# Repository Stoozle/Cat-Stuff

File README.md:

# FLOPS (FeLine Obesity Prevention System)
## High level description (project in development and much is subject to change and refinement)
* Cat owner's may want to monitor their cat's weight for various reasons. This project is intended to provide a system that will automatically measures a cat's weight. Measurement data can be used to inform appropriate modifications to a cat's diet in order to meet a target weight.
## Theory of operation
* Takes a cat's weight measurement every time it sleeps in its bed
* Allows user to observe plot of weight measurements over time

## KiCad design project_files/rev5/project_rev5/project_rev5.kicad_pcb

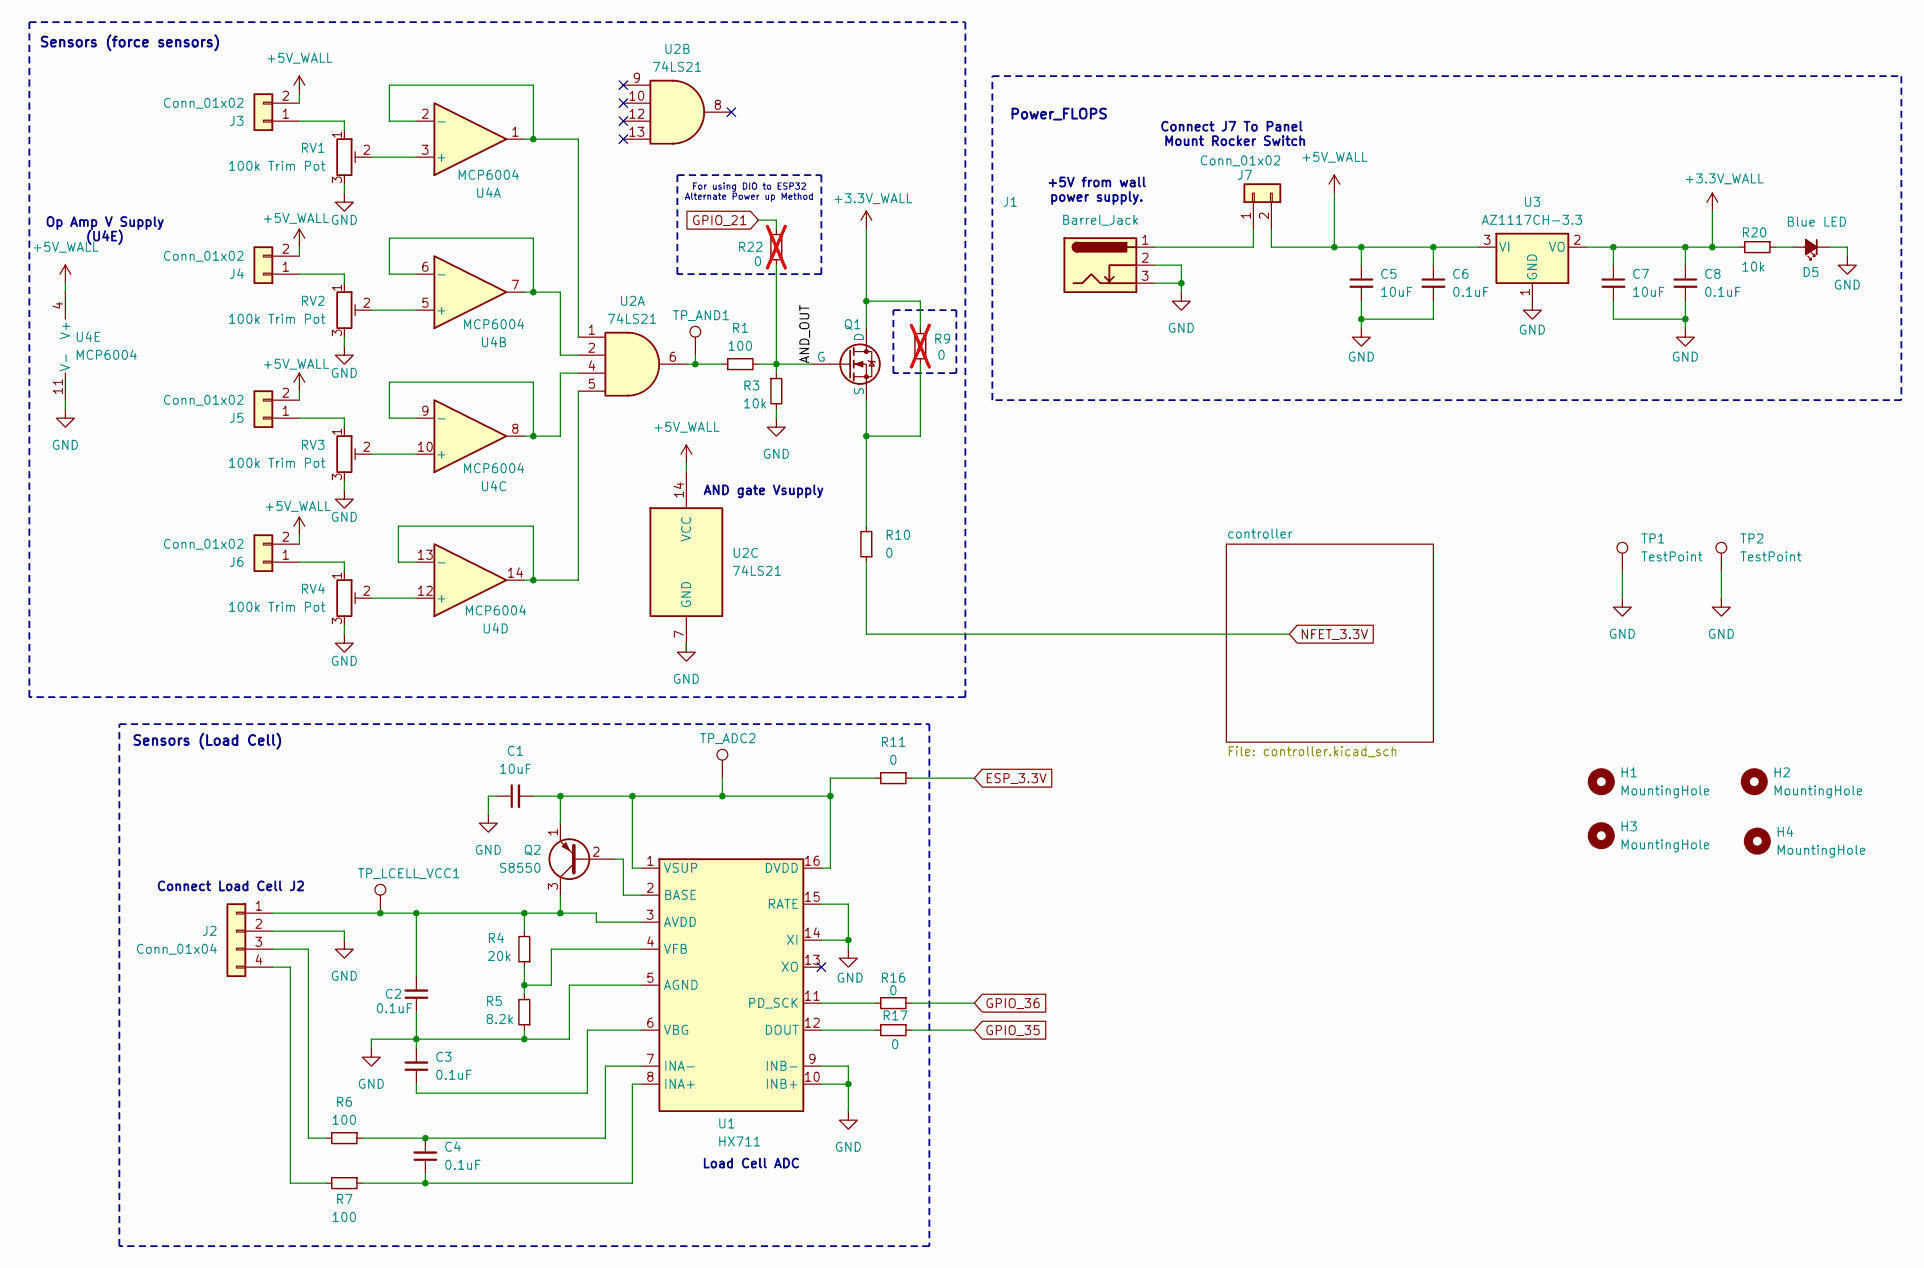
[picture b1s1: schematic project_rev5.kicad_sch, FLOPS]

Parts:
C1, C5, C7: 10uF; C_0603_1608Metric_Pad1.08x0.95mm_HandSolder
C2, C3, C4, C6, C8: 0.1uF; C_0603_1608Metric_Pad1.08x0.95mm_HandSolder
D5: 150060BS75000; LED_0603_1608Metric
H1, H2, H3, H4: MountingHole; MountingHole_3.2mm_M3_Pad
J1: Barrel_Jack; BarrelJack_Kycon_KLDX-0202-xC_Horizontal
J2: Conn_01x04; JST_XA_S04B-XASK-1N-BN_1x04_P2.50mm_Horizontal
J3, J4, J5, J6, J7: Conn_01x02; JST_XA_S02B-XASK-1N-BN_1x02_P2.50mm_Horizontal
Q1: BSS816NWH6327XTSA1; SOT-323_SC-70
Q2: S8550; SOT-23-3
R1, R6, R7: 100; R_0603_1608Metric_Pad0.98x0.95mm_HandSolder
R3, R20: 10k; R_0603_1608Metric_Pad0.98x0.95mm_HandSolder
R4: 20k; R_0603_1608Metric_Pad0.98x0.95mm_HandSolder
R5: 8.2k; R_0603_1608Metric_Pad0.98x0.95mm_HandSolder
R9, R22: 0; R_0603_1608Metric_Pad0.98x0.95mm_HandSolder; not fitted
R10, R11, R16, R17: 0; R_0603_1608Metric_Pad0.98x0.95mm_HandSolder
RV1, RV2, RV3, RV4: 100k Trim Pot; Potentiometer_Bourns_TC33X_Vertical
TP1, TP2: TestPoint; TestPoint_Keystone_5015_Micro-Minature
TP_ADC2: TestPoint; TestPoint_THTPad_D1.5mm_Drill0.7mm
TP_AND1: TestPoint; TestPoint_THTPad_D1.5mm_Drill0.7mm
TP_LCELL_VCC1: TestPoint; TestPoint_THTPad_D1.5mm_Drill0.7mm
U1: HX711; SOP-16_3.9x9.9mm_P1.27mm
U2: 74LS21; SOIC-14_3.9x8.7mm_P1.27mm
U3: AZ1117CH-3.3; SOT-223-3_TabPin2
U4: MCP6004; SOIC-14_3.9x8.7mm_P1.27mm

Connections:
+3.3V_WALL: C7.1, C8.1, Q1.1 (D), R9.2, R20.2, U3.2 (VO)
+5V_WALL: C5.1, C6.1, J3.2, J4.2, J5.2, J6.2, J7.2, U2.14 (VCC), U3.3 (VI), U4.4 (V+)
/AND_OUT: Q1.2 (G), R1.2, R3.1, R22.1
ESP_3.3V: R11.1; also elsewhere on the board
GND: C1.1, C2.1, C3.2, C5.2, C6.2, C7.2, C8.2, D5.1 (K), J1.2, J1.3, J2.2, R3.2, R5.1, RV1.3, RV2.3, RV3.3, RV4.3, TP1.1, TP2.1, U1.5 (AGND), U1.9 (INB-), U1.10 (INB+), U1.14 (XI), U1.15 (RATE), U2.7 (GND), U3.1 (GND), U4.11 (V-); also elsewhere on the board
GPIO_21: R22.2; also elsewhere on the board
GPIO_35: R17.1; also elsewhere on the board
GPIO_36: R16.1; also elsewhere on the board
NFET_3.3V: R10.1; also elsewhere on the board
unnamed: D5.2 (A), R20.1
unnamed: C2.2, J2.1, Q2.3 (C), R4.2, TP_LCELL_VCC1.1, U1.3 (AVDD)
unnamed: J2.3, R6.2
unnamed: J2.4, R7.2
unnamed: J3.1, RV1.1
unnamed: J4.1, RV2.1
unnamed: J5.1, RV3.1
unnamed: J6.1, RV4.1
unnamed: J1.1, J7.1
unnamed: Q1.3 (S), R9.1, R10.2
unnamed: Q2.2 (B), U1.2 (BASE)
unnamed: C1.2, Q2.1 (E), R11.2, TP_ADC2.1, U1.1 (VSUP), U1.16 (DVDD)
unnamed: R1.1, TP_AND1.1, U2.6
unnamed: R17.2, U1.12 (DOUT)
unnamed: C4.1, R7.1, U1.8 (INA+)
unnamed: C4.2, R6.1, U1.7 (INA-)
unnamed: R16.2, U1.11 (PD_SCK)
unnamed: C3.1, U1.6 (VBG)
unnamed: R4.1, R5.2, U1.4 (VFB)
unnamed: RV1.2, U4.3 (+)
unnamed: U2.1, U4.1, U4.2 (-)
unnamed: RV2.2, U4.5 (+)
unnamed: U2.2, U4.6 (-), U4.7
unnamed: RV3.2, U4.10 (+)
unnamed: U2.4, U4.8, U4.9 (-)
unnamed: RV4.2, U4.12 (+)
unnamed: U2.5, U4.13 (-), U4.14

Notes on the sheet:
Connect J7 To Panel Mount Rocker Switch
Power_FLOPS
+5V from wall power supply.
Op Amp V Supply (U4E)
Sensors (Load Cell)
Load Cell ADC
For using DIO to ESP32 Alternate Power up Method
Sensors (force sensors)
Connect Load Cell J2
AND gate Vsupply

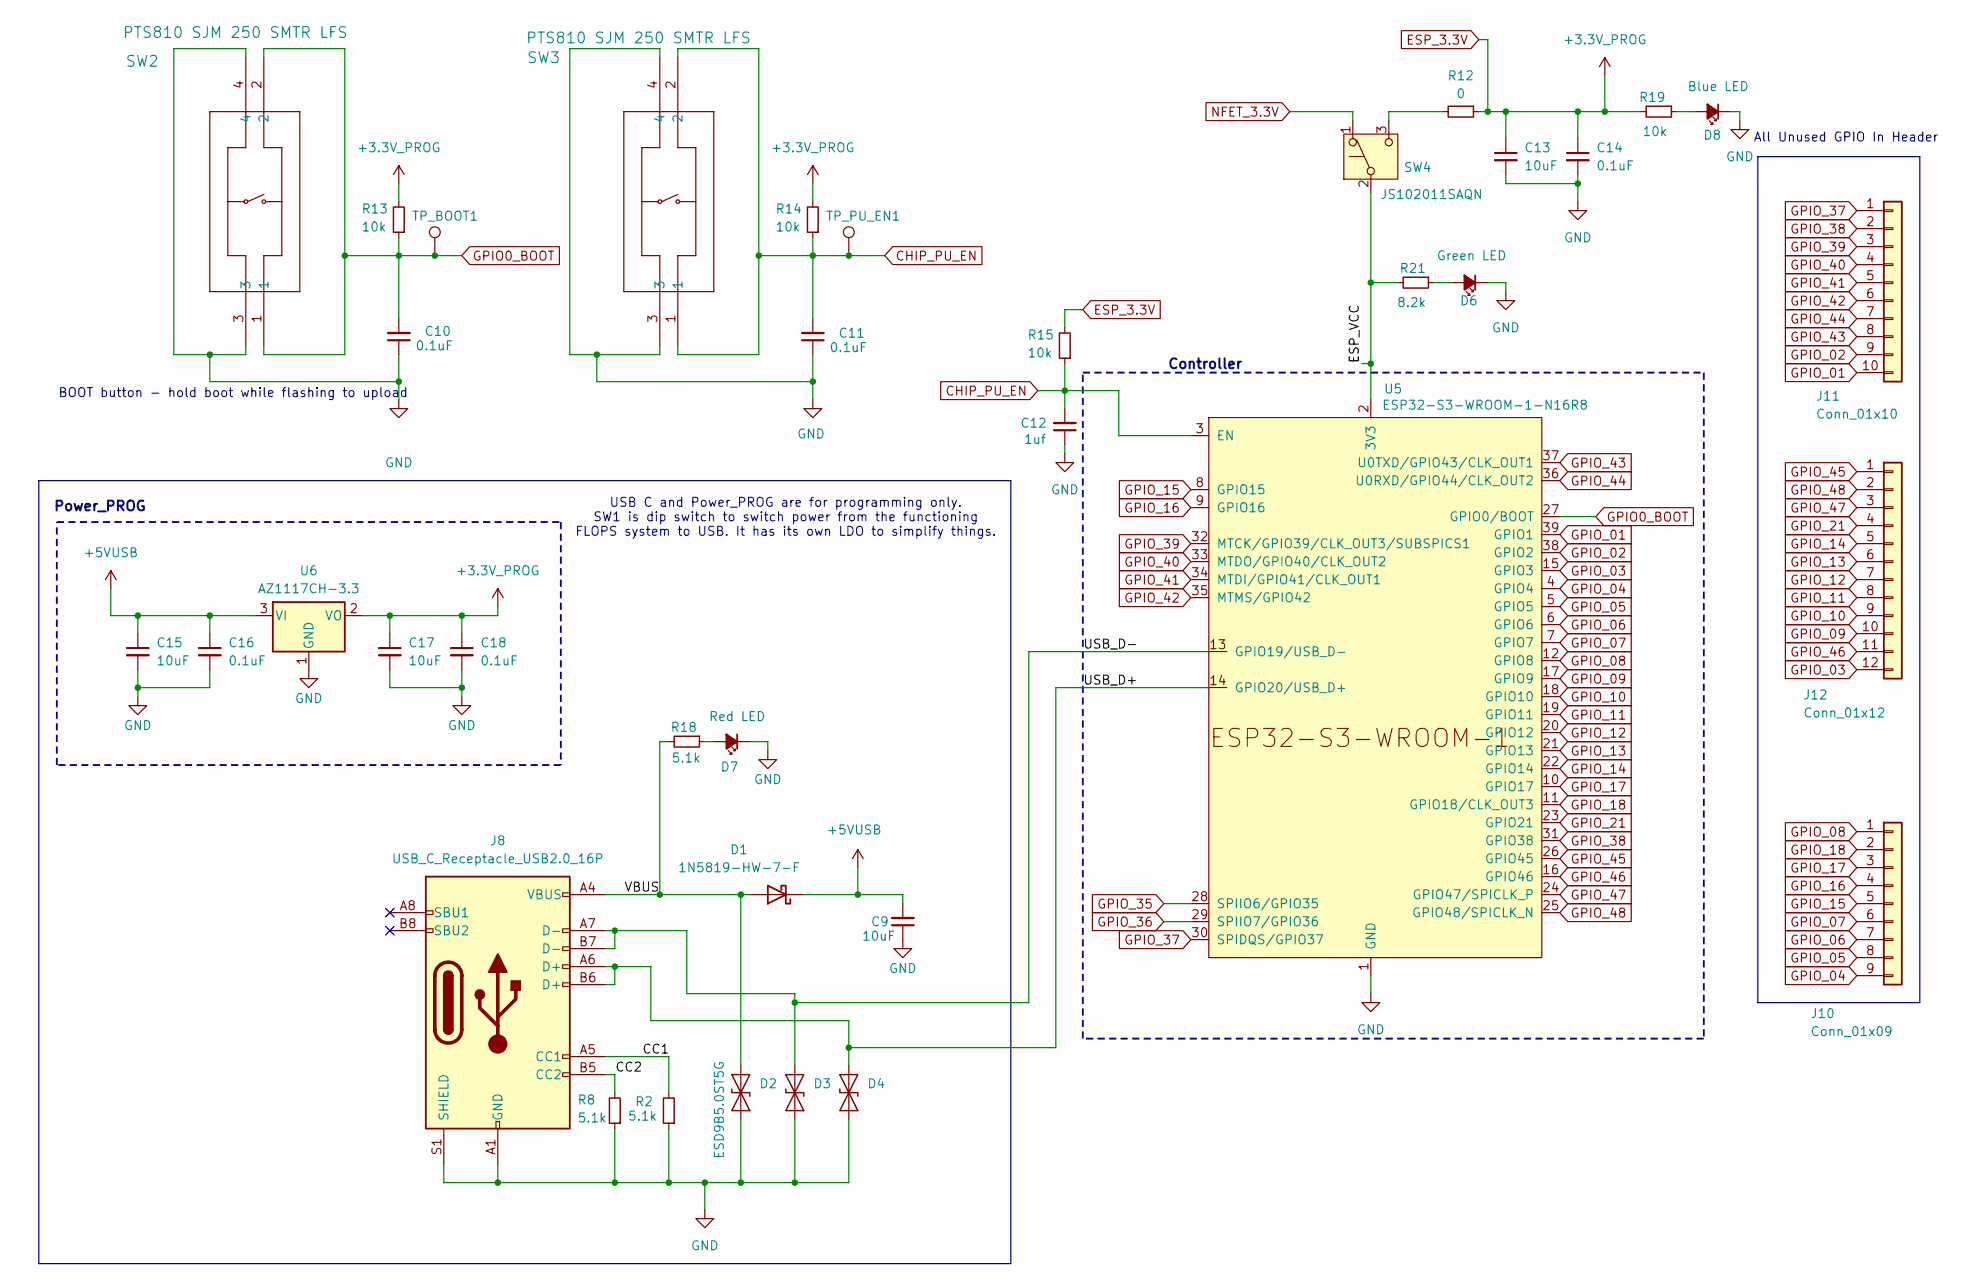
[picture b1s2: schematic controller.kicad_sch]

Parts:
C9, C13, C15, C17: 10uF; C_0603_1608Metric_Pad1.08x0.95mm_HandSolder
C10, C11, C14, C16, C18: 0.1uF; C_0603_1608Metric_Pad1.08x0.95mm_HandSolder
C12: 1uf; C_0603_1608Metric_Pad1.08x0.95mm_HandSolder
D1: 1N5819-HW-7-F; D_SOD-123
D2, D3, D4: ESD9B5.0ST5G; D_SOD-923
D6, D8: 150060BS75000; LED_0603_1608Metric
D7: 150060RS75000; LED_0603_1608Metric
J8: USB_C_Receptacle_USB2.0_16P; USB_C_Receptacle_GCT_USB4105-xx-A_16P_TopMnt_Horizontal
J10: Conn_01x09; PinHeader_1x09_P2.54mm_Vertical
J11: Conn_01x10; PinHeader_1x10_P2.54mm_Vertical
J12: Conn_01x12; PinHeader_1x12_P2.54mm_Vertical
R2, R8, R18: 5.1k; R_0603_1608Metric_Pad0.98x0.95mm_HandSolder
R12: 0; R_0603_1608Metric_Pad0.98x0.95mm_HandSolder
R13, R14, R15, R19: 10k; R_0603_1608Metric_Pad0.98x0.95mm_HandSolder
R21: 8.2k; R_0603_1608Metric_Pad0.98x0.95mm_HandSolder
SW2, SW3: PTS810 SJM 250 SMTR LFS; PTS810_CNK
SW4: JS102011SAQN; SW_SPDT_CK_JS102011SAQN
TP_BOOT1: TestPoint; TestPoint_THTPad_D1.5mm_Drill0.7mm
TP_PU_EN1: TestPoint; TestPoint_THTPad_D1.5mm_Drill0.7mm
U5: ESP32-S3-WROOM-1-N16R8; ESP32-S3-WROOM-1
U6: AZ1117CH-3.3; SOT-223-3_TabPin2

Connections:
+5VUSB: C9.2, C15.1, C16.1, D1.1 (K), U6.3 (VI)
/controller/CC1: J8.A5 (CC1), R2.2
/controller/CC2: J8.B5 (CC2), R8.2
/controller/ESP_VCC: R21.2, SW4.2 (B), U5.2 (3V3)
/controller/USB_D+: D4.1 (A1), J8.A6 (D+), J8.B6 (D+), U5.14 (GPIO20/USB_D+)
/controller/USB_D-: D3.1 (A1), J8.A7 (D-), J8.B7 (D-), U5.13 (GPIO19/USB_D-)
/controller/VBUS: D1.2 (A), D2.1 (A1), J8.A4 (VBUS), J8.A9 (VBUS), J8.B4 (VBUS), J8.B9 (VBUS), R18.2
CHIP_PU_EN: C11.2, C12.2, R14.1, R15.1, SW3.1, SW3.2, TP_PU_EN1.1, U5.3 (EN)
ESP_3.3V: C13.1, C14.1, C17.1, C18.1, R12.1, R13.2, R14.2, R15.2, R19.2, U6.2 (VO); also elsewhere on the board
GND: C9.1, C10.1, C11.1, C12.1, C13.2, C14.2, C15.2, C16.2, C17.2, C18.2, D2.2 (A2), D3.2 (A2), D4.2 (A2), D6.1 (K), D7.1 (K), D8.1 (K), J8.A1 (GND), J8.A12 (GND), J8.B1 (GND), J8.B12 (GND), J8.S1 (SHIELD), R2.1, R8.1, SW2.3, SW2.4, SW3.3, SW3.4, U5.1 (GND), U5.40 (GND), U5.41 (GND), U6.1 (GND); also elsewhere on the board
GPIO0_BOOT: C10.2, R13.1, SW2.1, SW2.2, TP_BOOT1.1, U5.27 (GPIO0/BOOT)
GPIO_01: J11.10, U5.39 (GPIO1)
GPIO_02: J11.9, U5.38 (GPIO2)
GPIO_03: J12.12, U5.15 (GPIO3)
GPIO_04: J10.9, U5.4 (GPIO4)
GPIO_05: J10.8, U5.5 (GPIO5)
GPIO_06: J10.7, U5.6 (GPIO6)
GPIO_07: J10.6, U5.7 (GPIO7)
GPIO_08: J10.1, U5.12 (GPIO8)
GPIO_09: J12.10, U5.17 (GPIO9)
GPIO_10: J12.9, U5.18 (GPIO10)
GPIO_11: J12.8, U5.19 (GPIO11)
GPIO_12: J12.7, U5.20 (GPIO12)
GPIO_13: J12.6, U5.21 (GPIO13)
GPIO_14: J12.5, U5.22 (GPIO14)
GPIO_15: J10.5, U5.8 (GPIO15)
GPIO_16: J10.4, U5.9 (GPIO16)
GPIO_17: J10.3, U5.10 (GPIO17)
GPIO_18: J10.2, U5.11 (GPIO18/CLK_OUT3)
GPIO_21: J12.4, U5.23 (GPIO21); also elsewhere on the board
GPIO_35: U5.28 (SPIIO6/GPIO35); also elsewhere on the board
GPIO_36: U5.29 (SPIIO7/GPIO36); also elsewhere on the board
GPIO_37: J11.1, U5.30 (SPIDQS/GPIO37)
GPIO_38: J11.2, U5.31 (GPIO38)
GPIO_39: J11.3, U5.32 (MTCK/GPIO39/CLK_OUT3/SUBSPICS1)
GPIO_40: J11.4, U5.33 (MTDO/GPIO40/CLK_OUT2)
GPIO_41: J11.5, U5.34 (MTDI/GPIO41/CLK_OUT1)
GPIO_42: J11.6, U5.35 (MTMS/GPIO42)
GPIO_43: J11.8, U5.37 (U0TXD/GPIO43/CLK_OUT1)
GPIO_44: J11.7, U5.36 (U0RXD/GPIO44/CLK_OUT2)
GPIO_45: J12.1, U5.26 (GPIO45)
GPIO_46: J12.11, U5.16 (GPIO46)
GPIO_47: J12.3, U5.24 (GPIO47/SPICLK_P)
GPIO_48: J12.2, U5.25 (GPIO48/SPICLK_N)
NFET_3.3V: SW4.1 (A); also elsewhere on the board
unnamed: D6.2 (A), R21.1
unnamed: D7.2 (A), R18.1
unnamed: D8.2 (A), R19.1
unnamed: R12.2, SW4.3 (C)

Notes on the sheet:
Controller
All Unused GPIO In Header
USB C and Power_PROG are for programming only. SW1 is dip switch to switch power from the functioning FLOPS system to USB. It has its own LDO to simplify things.
BOOT button - hold boot while flashing to upload
Power_PROG

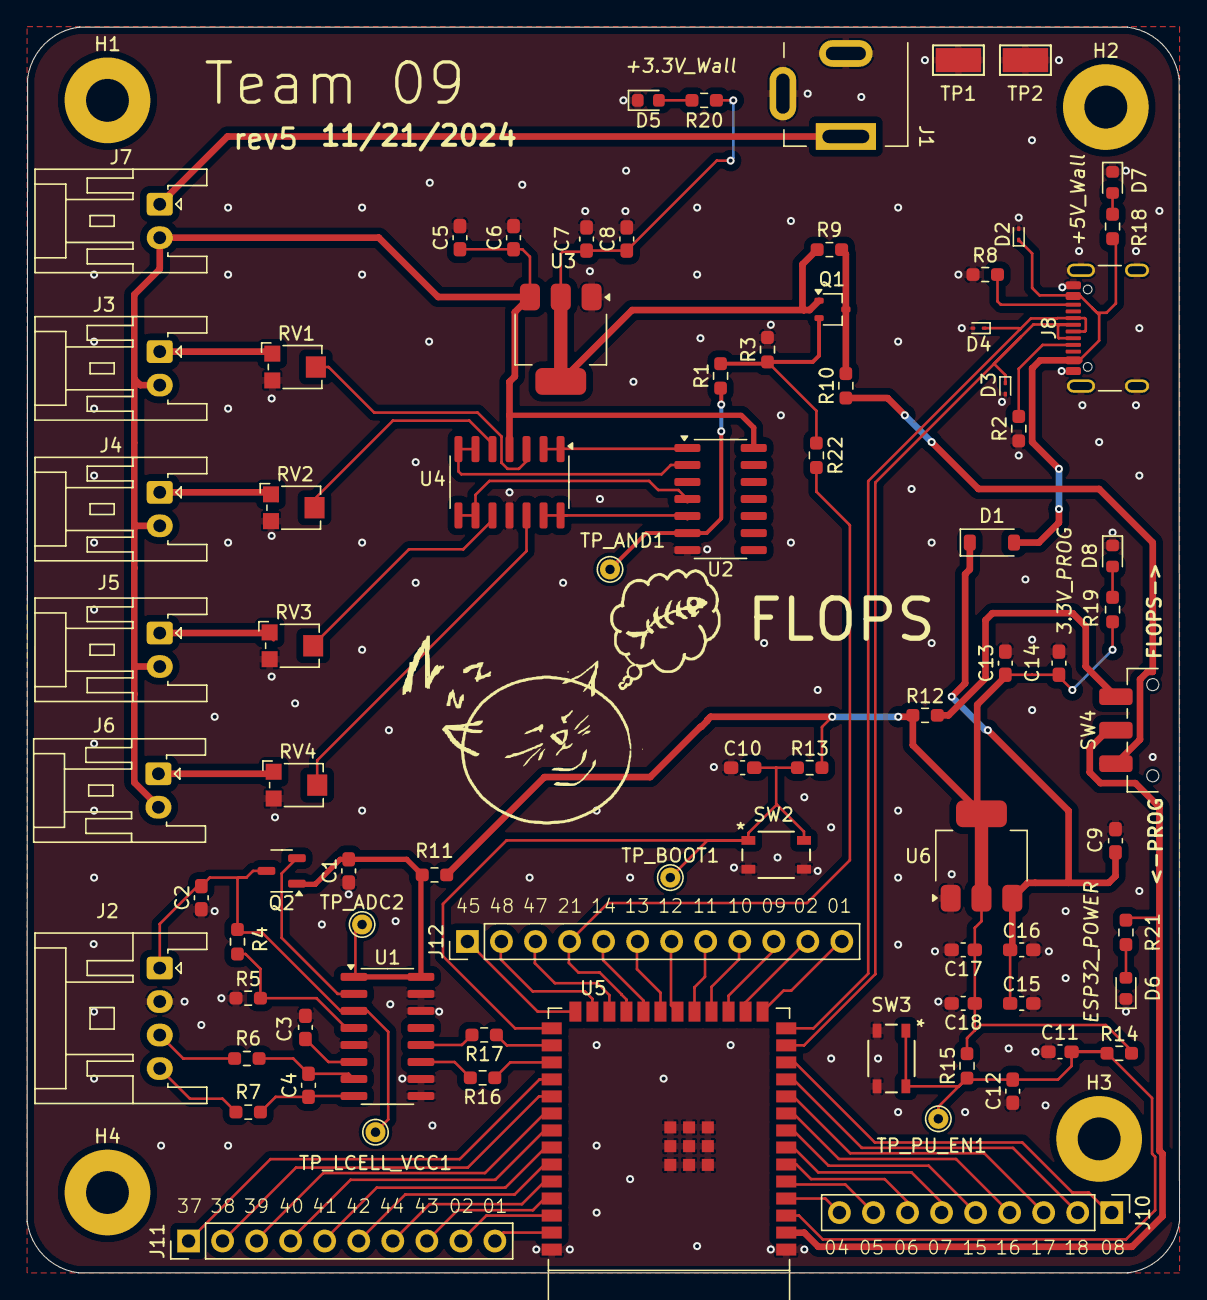
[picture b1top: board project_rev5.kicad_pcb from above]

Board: 2 copper layers, 86.0 x 93.0 mm, 85 parts (0 on the bottom side), 79 nets.

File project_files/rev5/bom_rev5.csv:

Reference,Value,Datasheet,Footprint,Qty,DNP
"C1,C5,C7,C9,C13,C15,C17",10uF,~,Capacitor_SMD:C_0603_1608Metric_Pad1.08x0.95mm_HandSolder,7,
"C2,C3,C4,C6,C8,C10,C11,C14,C16,C18",0.1uF,~,Capacitor_SMD:C_0603_1608Metric_Pad1.08x0.95mm_HandSolder,10,
C12,1uf,~,Capacitor_SMD:C_0603_1608Metric_Pad1.08x0.95mm_HandSolder,1,
D1,1N5819-HW-7-F,http://www.vishay.com/docs/88525/1n5817.pdf,Diode_SMD:D_SOD-123,1,
"D2,D3,D4",ESD9B5.0ST5G,https://www.onsemi.com/pub/Collateral/ESD9B-D.PDF,Diode_SMD:D_SOD-923,3,
"D5,D6,D8",150060BS75000,~,LED_SMD:LED_0603_1608Metric,3,
D7,150060RS75000,~,LED_SMD:LED_0603_1608Metric,1,
J1,Barrel_Jack,~,Connector_BarrelJack:BarrelJack_Kycon_KLDX-0202-xC_Horizontal,1,
J2,Conn_01x04,~,Connector_JST:JST_XA_S04B-XASK-1N-BN_1x04_P2.50mm_Horizontal,1,
"J3,J4,J5,J6,J7",Conn_01x02,~,Connector_JST:JST_XA_S02B-XASK-1N-BN_1x02_P2.50mm_Horizontal,5,
J8,USB_C_Receptacle_USB2.0_16P,https://www.usb.org/sites/default/files/documents/usb_type-c.zip,Connector_USB:USB_C_Receptacle_GCT_USB4105-xx-A_16P_TopMnt_Horizontal,1,
J10,Conn_01x09,~,Connector_PinHeader_2.54mm:PinHeader_1x09_P2.54mm_Vertical,1,
J11,Conn_01x10,~,Connector_PinHeader_2.54mm:PinHeader_1x10_P2.54mm_Vertical,1,
J12,Conn_01x12,~,Connector_PinHeader_2.54mm:PinHeader_1x12_P2.54mm_Vertical,1,
Q1,BSS816NWH6327XTSA1,https://ngspice.sourceforge.io/docs/ngspice-html-manual/manu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,Package_TO_SOT_SMD:SOT-323_SC-70,1,
Q2,S8550,http://www.unisonic.com.tw/datasheet/S8550.pdf,Package_TO_SOT_SMD:SOT-23-3,1,
"R1,R6,R7",100,~,Resistor_SMD:R_0603_1608Metric_Pad0.98x0.95mm_HandSolder,3,
"R2,R8,R18",5.1k,~,Resistor_SMD:R_0603_1608Metric_Pad0.98x0.95mm_HandSolder,3,
"R3,R13,R14,R15,R19,R20",10k,~,Resistor_SMD:R_0603_1608Metric_Pad0.98x0.95mm_HandSolder,6,
R4,20k,~,Resistor_SMD:R_0603_1608Metric_Pad0.98x0.95mm_HandSolder,1,
"R5,R21",8.2k,~,Resistor_SMD:R_0603_1608Metric_Pad0.98x0.95mm_HandSolder,2,
"R9,R22",0,~,Resistor_SMD:R_0603_1608Metric_Pad0.98x0.95mm_HandSolder,2,DNP
"R10,R11,R12,R16,R17",0,~,Resistor_SMD:R_0603_1608Metric_Pad0.98x0.95mm_HandSolder,5,
"RV1,RV2,RV3,RV4",100k Trim Pot,~,Potentiometer_SMD:Potentiometer_Bourns_TC33X_Vertical,4,
"SW2,SW3",PTS810 SJM 250 SMTR LFS,PTS810 SJM 250 SMTR LFS,PTS810SJM250SMTR LFS:PTS810_CNK,2,
SW4,JS102011SAQN,~,Button_Switch_SMD:SW_SPDT_CK_JS102011SAQN,1,
"TP1,TP2,TP_ADC2,TP_AND1,TP_BOOT1,TP_LCELL_VCC1,TP_PU_EN1",TestPoint,~,-- mixed values --,7,
U1,HX711,https://web.archive.org/web/20220615044707/https://akizukide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,Package_SO:SOP-16_3.9x9.9mm_P1.27mm,1,
U2,74LS21,http://www.ti.com/lit/gpn/sn74LS21,Package_SO:SOIC-14_3.9x8.7mm_P1.27mm,1,
"U3,U6",AZ1117CH-3.3,https://www.diodes.com/assets/Datasheets/AZ1117.pdf,Package_TO_SOT_SMD:SOT-223-3_TabPin2,2,
U4,MCP6004,http://ww1.microchip.com/downloads/en/DeviceDoc/21733j.pdf,Package_SO:SOIC-14_3.9x8.7mm_P1.27mm,1,
U5,ESP32-S3-WROOM-1-N16R8,https://www.espressif.com/sites/default/files/documentation/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,PCM_Espressif:ESP32-S3-WROOM-1,1,

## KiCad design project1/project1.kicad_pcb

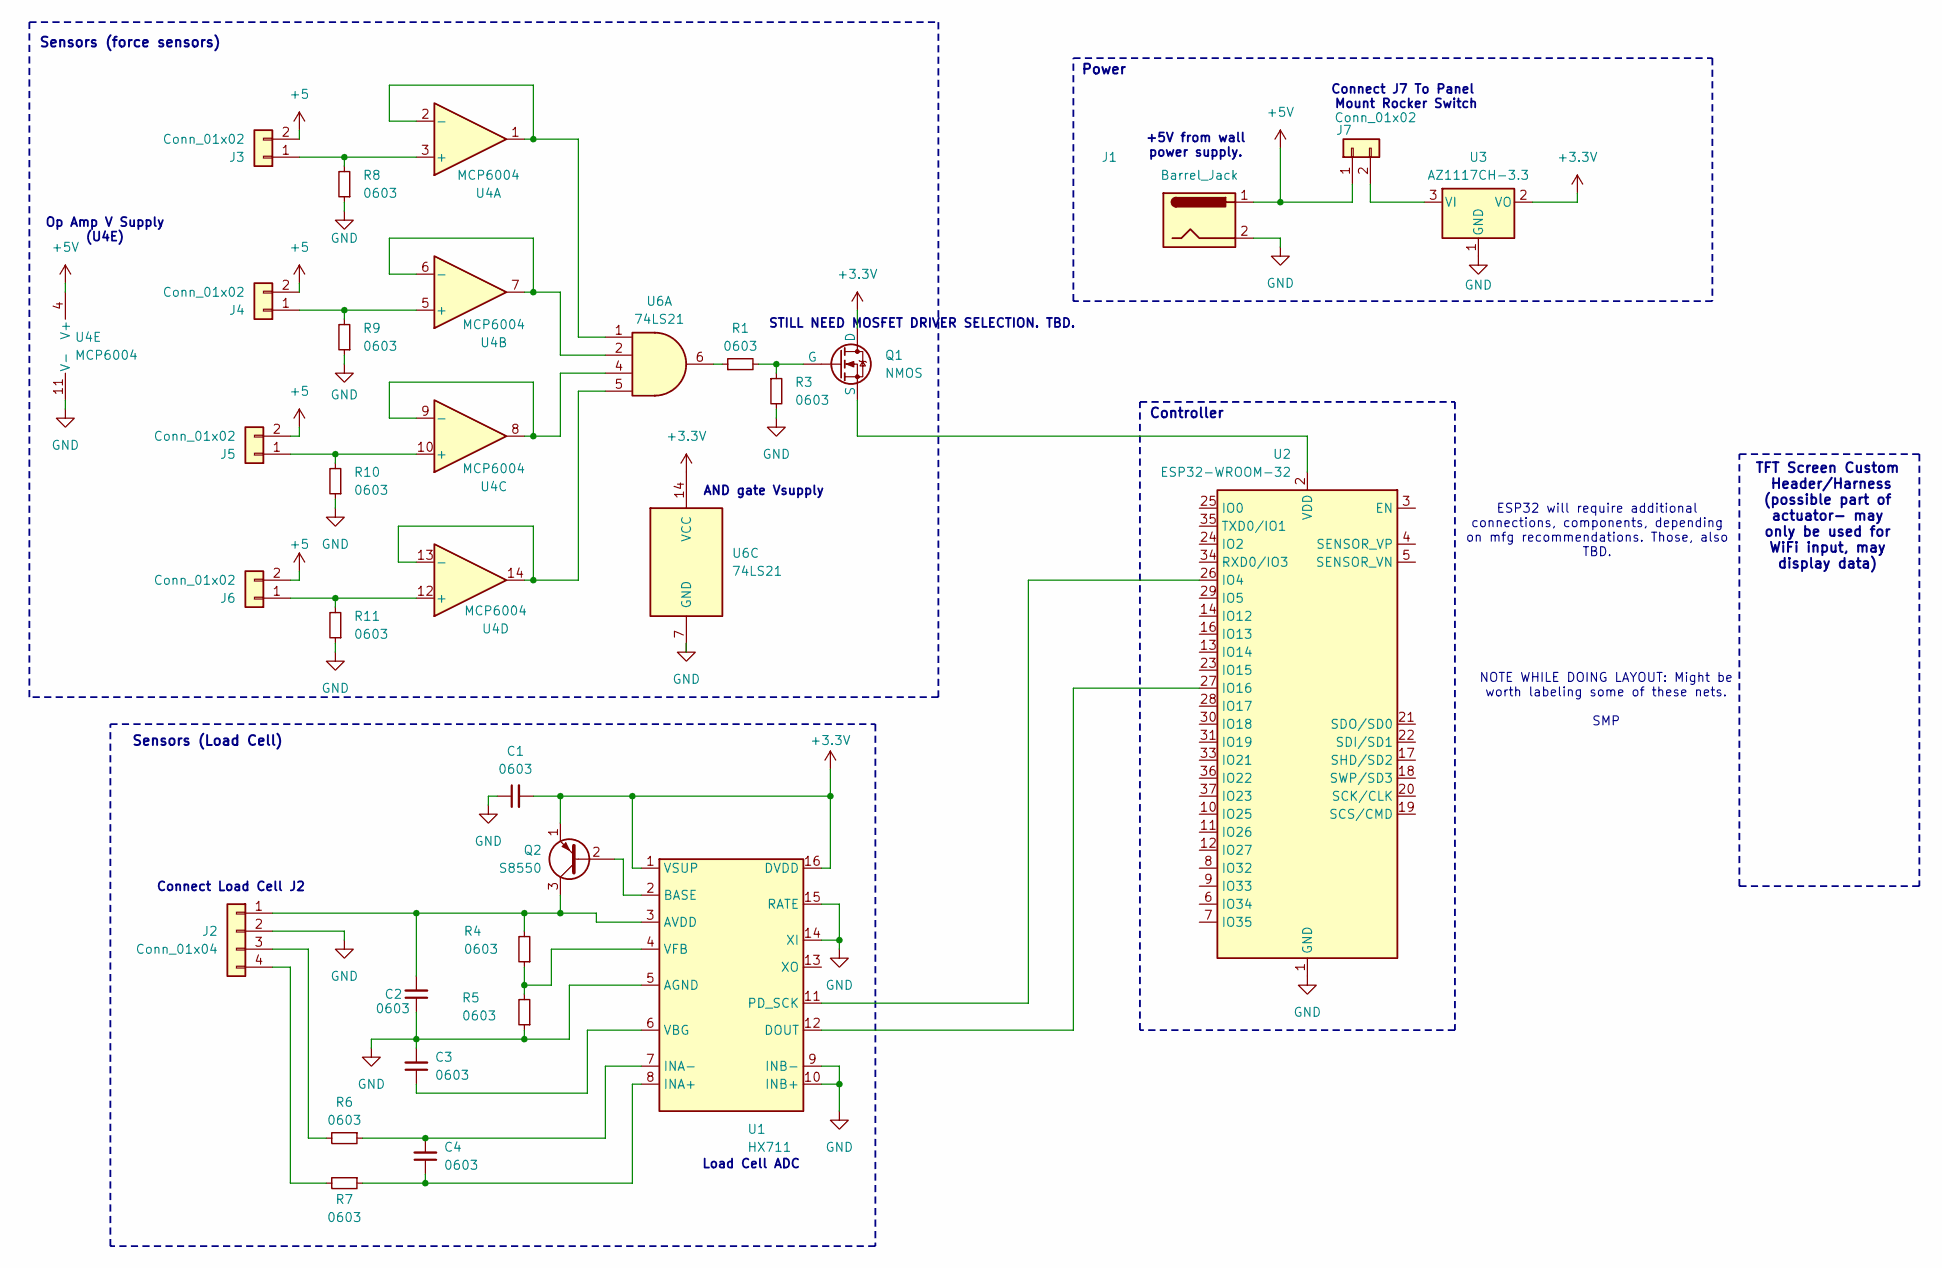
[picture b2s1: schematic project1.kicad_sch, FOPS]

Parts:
C1, C2, C3, C4: 0603; C_0201_0603Metric
J1: Barrel_Jack; BarrelJack_Kycon_KLDX-0202-xC_Horizontal
J2: Conn_01x04; JST_XA_S04B-XASK-1N-BN_1x04_P2.50mm_Horizontal
J3, J4, J5, J6, J7: Conn_01x02; JST_XA_S02B-XASK-1_1x02_P2.50mm_Horizontal
Q1: NMOS; SOT-323_SC-70
Q2: S8550; SOT-23-3
R1, R3: 0603
R4, R5, R6, R7, R8, R9, R10, R11: 0603; R_0201_0603Metric
U1: HX711; SOP-16_3.9x9.9mm_P1.27mm
U2: ESP32-WROOM-32
U3: AZ1117CH-3.3; SOT-223
U4: MCP6004; SOIC-14_3.9x8.7mm_P1.27mm
U6: 74LS21; SO-14_5.3x10.2mm_P1.27mm

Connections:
+3.3V: C1.2, Q1.1 (D), Q2.1 (E), U1.1 (VSUP), U1.16 (DVDD), U3.2 (VO), U6.14 (VCC)
+5: J3.2, J4.2, J5.2, J6.2
+5V: J1.1, J7.1, U4.4 (V+)
GND: C1.1, C2.1, C3.2, J1.2, J2.2, R3.2, R5.1, R8.1, R9.1, R10.1, R11.1, U1.5 (AGND), U1.9 (INB-), U1.10 (INB+), U1.14 (XI), U1.15 (RATE), U2.1 (GND), U2.15 (GND), U2.38 (GND), U2.39 (GND), U3.1 (GND), U4.11 (V-), U6.7 (GND)
unnamed: C2.2, J2.1, Q2.3 (C), R4.2, U1.3 (AVDD)
unnamed: J2.3, R6.2
unnamed: J2.4, R7.2
unnamed: J3.1, R8.2, U4.3 (+)
unnamed: J4.1, R9.2, U4.5 (+)
unnamed: J5.1, R10.2, U4.10 (+)
unnamed: J6.1, R11.2, U4.12 (+)
unnamed: J7.2, U3.3 (VI)
unnamed: Q1.2 (G), R1.2, R3.1
unnamed: Q1.3 (S), U2.2 (VDD)
unnamed: Q2.2 (B), U1.2 (BASE)
unnamed: R1.1, U6.6
unnamed: U1.12 (DOUT), U2.27 (IO16)
unnamed: C4.1, R7.1, U1.8 (INA+)
unnamed: C4.2, R6.1, U1.7 (INA-)
unnamed: U1.11 (PD_SCK), U2.26 (IO4)
unnamed: C3.1, U1.6 (VBG)
unnamed: R4.1, R5.2, U1.4 (VFB)
unnamed: U4.1, U4.2 (-), U6.1
unnamed: U4.6 (-), U4.7, U6.2
unnamed: U4.8, U4.9 (-), U6.4
unnamed: U4.13 (-), U4.14, U6.5

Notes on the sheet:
Connect J7 To Panel Mount Rocker Switch
ESP32 will require additional connections, components, depending on mfg recommendations. Those, also TBD.
Controller
Power
+5V from wall power supply.
Op Amp V Supply (U4E)
Sensors (Load Cell)
Load Cell ADC
STILL NEED MOSFET DRIVER SELECTION. TBD.
NOTE WHILE DOING LAYOUT: Might be worth labeling some of these nets. SMP
Sensors (force sensors)
Connect Load Cell J2
TFT Screen Custom Header/Harness (possible part of actuator- may only be used for WiFi input, may display data)
AND gate Vsupply

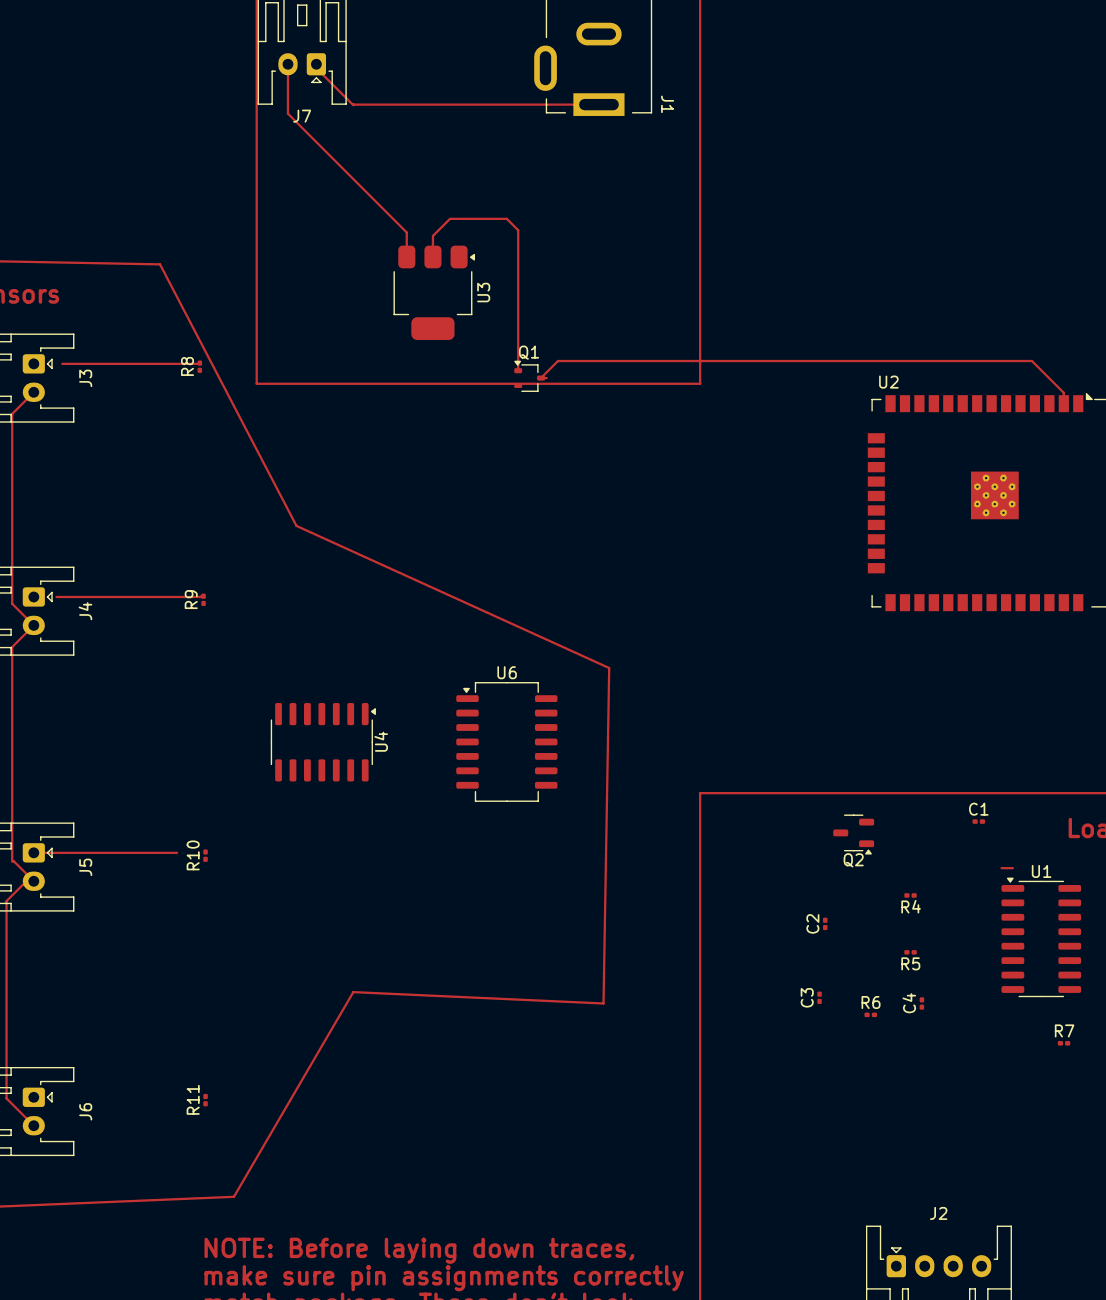
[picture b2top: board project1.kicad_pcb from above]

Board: 2 copper layers, 26 parts (0 on the bottom side), 24 nets.

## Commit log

2024-10-16 Create test
    This is only a test to see how the system works.
2024-10-16 Update test
    Another test
2024-10-16 Update test (#1)
    Another test
2024-10-16 Update test (#2)
    Another test
2024-10-31 update test.txt
    just added some stuff to test behavior
2024-10-31 rev 1 for preliminary schematic) asdf
2024-10-31 adding first version of pds to repo. make changes and re-commit.
2024-10-31 added rev # to document for rev1
2024-11-04 deleted pds docx, added pdf of rev1, added pdf of rev2
2024-11-04 just a test
2024-11-04 just a test (#14)
2024-11-06 a line was added
2024-11-07 committing pcb and some other cache files
2024-11-07 adding outline for gantt chart update
2024-11-07 adding outline for gantt chart update (#22)
2024-11-07 update schematic, added footprints, started layout.
2024-11-07 Stu schem update (#23)
    * adding outline for gantt chart update
    * update schematic, added footprints, started layout.
2024-11-07 a couple changes
2024-11-07 added breadboard image, video of load cell weighing a la croix and force sensor on o-scope
2024-11-07 added markdown for brief status report.
2024-11-07 Stu schem update (#25)
    * adding outline for gantt chart update
    * update schematic, added footprints, started layout.
    * a couple changes
    * added breadboard image, video of load cell weighing a la croix and force sensor on o-scope
    * added markdown for brief status report.
2024-11-07 changed pdf of pcb and sch
2024-11-07 trying again to upload these pdfs
2024-11-07 trying again to upload these pdfs (#26)
2024-11-07 Revision of Gannt Chart
    - Created using Gannt Project
2024-11-12 Test run two
2024-11-12 test run three
2024-11-12 BOM Updated Progress
2024-11-12 BOM Update
2024-11-12 BOM Official Rough Draft Update
2024-11-13 BOM Official RD in progress
2024-11-14 BOM Official Rough Draft in-progress
2024-11-14 BOM Official Rough Draft
2024-11-14 BOM Official
2024-11-14 Bom branch (#31)
    * Test run two
    * test run three
    * BOM Updated Progress
    * BOM Update
    * BOM Official Rough Draft Update
    * BOM Official RD in progress
2024-11-14 renamed project to current rev. each future rev will get it's own copy in project directory. each rev will not be touched once it has been committed and another rev is being worked on. Added update s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
2024-11-14 added labels to rev3 sch and pcb
2024-11-14 printed pdf of sch and pcb
2024-11-14 moved something
2024-11-14 rev3 schematic and layout (#32)
    * renamed project to current rev. each future rev will get it's own copy in project directory. each rev will not be touched once it has been committed and another rev is being worked on. Added update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
    * added labels to rev3 sch and pcb
    * printed pdf of sch and pcb
    * moved something
2024-11-14 made me commit this
2024-11-18 making a commit, didn't mean to do it on main but here we are
2024-11-18 fucked up a commit, tring to fix
2024-11-18 added new project for rev4 and reverted changes for rev3
2024-11-20 committing update
2024-11-20 final rev4
2024-11-20 added updates to rev5!
2024-11-21 pushing final rev5. may god have mercy.
2024-11-21 last adds of pdf of sch and pcb
2024-11-23 Initial Prototype of Server In Python
2024-11-23 Working Server
    Server runs, is hosted on the correct domain and is able to correctly handle data, generating requisite plots
2024-11-23 Basic Server on the ESP32
    Server implementation on ESP32 to send data to web server
2024-11-23 Configuration to setup reverse proxy using NGINX
2024-11-23 adding basic code for load cell. One for calibrating, one for collecting weight.
2024-11-24 Update server_esp32.c
    Added ability to read from value HX711 and send it to web server
2024-11-26 updating PDS rev 3
2024-11-26 adding some images from previous force sensor and load cell testing.
2024-12-11 final BOM updated
2024-12-12 setting this stuff aside from now
2024-12-12 adding that code for mohammad
2024-12-12 updated L1
2024-12-12 seriously, the last one
2024-12-12 temp scale code for test before demo
